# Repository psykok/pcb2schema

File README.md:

# pcb2schema

A KiCad addon that runs the design flow backwards: draw a PCB, get a schematic.

Drop footprints in the PCB editor, draw tracks between their pads, then run the
plugin. It works out which library symbol each footprint represents, recovers the
netlist from the copper you drew, places the symbols and routes the connections as
orthogonal wires. References are annotated back into the board and linked to the
generated symbols, so KiCad's normal schematic↔PCB sync keeps working afterwards.

Built and tested against **KiCad 10.0.6**.

## Why this is not straightforward

KiCad has no schematic API. `kicad-cli sch` only exports, and the IPC API covers the
board. So the `.kicad_sch` is generated directly as S-expressions, which means the
writer has to be exactly faithful to KiCad's own format — verified by round-tripping
every KiCad file on the system byte-for-byte.

The other half is that a freshly drawn board usually has **no nets at all**: every pad
and track sits on netcode 0. KiCad's ratsnest is useless in that state, but its
geometric hit-testing is not, and a union-find over pads, tracks, vias and zones
rebuilds the netlist from what is physically touching what.

## Installing

```sh
python3 tools/build_pcm.py            # -> dist/pcb2schema-<version>.zip
```

Then **Plugin and Content Manager → Install from File…** and pick the zip. Restart
pcbnew, or use *Tools → External Plugins → Refresh Plugins*.

This is the route to use. PCM reads `metadata.json` out of the archive as it installs
and records the result in `installed_packages.json`; it never reads it back from the
installed directory. So a package only has an author, description and version if PCM
put it there.

For development there is also

```sh
python3 tools/build_pcm.py --install  # copy straight into the plugin folder
```

which gets the code under the toolbar button without going through PCM. The trade-off
is that PCM has no record of it, so it appears in the package list with a blank author
and version 0.0. That listing is cosmetic -- the plugin itself works either way.

The installed layout matters and is easy to get wrong: KiCad imports each directory
under `<KICAD_3RD_PARTY>/plugins/` *as a Python module*, and skips any that has no
`__init__.py` at its top level. So the files must land at

```
~/Documents/KiCad/<ver>/3rdparty/plugins/pcb2schema/__init__.py
```

not one level deeper. The directory name also becomes the module name, so it has to be
a legal Python identifier — the dotted reverse-DNS identifier cannot be used here.
`build_pcm.py --install` does this and fails loudly if the marker file is missing.

## Using it

1. Open your board in the PCB editor and save it.
2. Close the **schematic** editor. The PCB editor can stay open — that's where the
   plugin runs from. Only eeschema is a conflict, because the `.kicad_sch` is written
   directly and would be discarded the next time eeschema saves. The board is updated
   in memory and saved by you as usual.
3. Click the **PCB to Schematic** toolbar button, or *Tools → External Plugins → PCB
   to Schematic*.
4. If anything is untagged, decide whether to auto-tag it (see below).
5. Confirm any footprints the matcher could not identify on its own.
6. Open the schematic to review.

Both files are backed up with a timestamp before anything is written.

### Two-step: arrange, then wire

The automatic placement is a grid. It echoes the board so the sheet is navigable, but
on any real design you will want to lay it out yourself — and the router should work
with *your* arrangement, not one you are about to discard. So the run can be split:

1. **Symbols only** — places every part and stops. Any existing wiring is left alone.
2. *Arrange the sheet in the schematic editor.*
3. **Nets only** — wires it up, keeping every symbol exactly where you put it.

The plugin asks which to do on each run; **Symbols and nets** does both in one pass and
is the default. From the command line:

```sh
tools/run_headless.py board.kicad_pcb --stage symbols   # place, then go arrange
tools/run_headless.py board.kicad_pcb --stage nets      # wire up your arrangement
```

Splitting the run changes only where things sit — the resulting netlist is identical
either way, which is asserted by a test.

Between the two steps the board may have moved on, so the second step reports what
changed: parts added, parts deleted, and footprints swapped for a different one.
Wiring against a stale sheet would otherwise produce a schematic that quietly
disagrees with the PCB.

### Re-running keeps what you have arranged

Symbol positions survive a re-run, and so does wiring. A net is redrawn only when
something about it actually changed — its name, its set of pins, or where those pins
sit. Everything else is left exactly as you arranged it, including routes you dragged
into shape by hand.

Move one symbol and only the nets touching it are redrawn; the rest of the sheet is
untouched. The run reports which is which:

```
Updated board.kicad_sch | 12 symbols, 10 nets, 8 net(s) left untouched
```

If part of a net's wiring has been deleted, that net is redrawn rather than left half
wired.

### Everything must be tagged first

A conversion is only as good as the identifiers it starts from. If footprints are
still `REF**` and nets are unnamed, the plugin would have to invent both — and then
write its inventions back onto your board. That is a naming decision, and it belongs
to you, so it is an explicit gate rather than a silent default.

Before generating anything the plugin checks for footprints with no reference
designator, duplicated references, and unnamed nets. If it finds any it stops, having
written nothing, and reports exactly what is missing. You can then either tag them
yourself in the PCB editor, or let the plugin do it:

```sh
tools/run_headless.py board.kicad_pcb            # reports and stops (exit 2)
tools/run_headless.py board.kicad_pcb --auto-tag # fills the gaps
```

Auto-tagging **only fills gaps**. It assigns the next free number to each untagged
item and never renames anything that already has one, so hand-assigned identifiers
survive untouched. Net numbering follows whatever convention the board already uses:
if your nets are called `1`, `2`, `3`, the next one is `4`, not `N$1`.

Duplicated references are reported but not fixed — which of two `R1`s should be
renamed is not something to guess at.

### Net names are preserved

Every net gets a **global** label carrying its name. This is not decoration: a wire
carries no name, so without a label KiCad renames the net `Net-(D1-A)`, and the next
*Update PCB from Schematic* pushes that back over the name you chose. Global rather
than local labels because KiCad prefixes a root-sheet local label with the sheet path
— a net called `1` would come back as `/1`.

### What it decides on its own

Everyday parts — resistors, capacitors, LEDs, diodes, crystals, fuses, switches, pin
headers, terminal blocks — are matched without asking, using the symbol's declared
footprint filters, its default footprint, and a curated hint table. Pin/pad
compatibility is a hard gate rather than a hint: a symbol whose pins cannot be
reconciled with the footprint's pads is never offered, however well it scores
otherwise.

Anything ambiguous goes to a picker showing the ranked candidates, why each was
suggested, and the pad-versus-pin comparison. A match that would need pads mapped to
pins positionally (`A`/`K` against `1`/`2`) is never auto-accepted — that is a guess
about polarity, and you should see it.

## Limitations

- **Placement is a grid, not a schematic layout.** Symbols keep their rough relative
  positions from the board, which makes the sheet navigable, but no attempt is made to
  produce a conventionally-drawn schematic (power at top, signal flow left to right).
- **Nets that cannot be routed become labels.** The result stays electrically correct;
  it just looks worse for that net. The run report lists them.
- **Genuinely unconnected pads stay unconnected.** No no-connect flags are inserted,
  so ERC will report them — that is usually a real layout problem worth seeing.
- **Duplicated references are not auto-fixed** — only reported.
- Placement of *new* symbols on an existing sheet is a grid slot, not a considered
  position; existing symbols never move.

## Development

Everything under `plugins/core/` is headless and must never import `wx`; the GUI layer
is confined to `plugins/action.py` and `plugins/ui/`. That is what lets the whole
pipeline be driven and tested without clicking through KiCad.

Tests run under KiCad's bundled interpreter, since `pcbnew` imports nowhere else, and
use a small built-in runner because that interpreter has no pytest:

```sh
/Applications/KiCad/KiCad.app/Contents/Frameworks/Python.framework/Versions/3.9/bin/python3 \
    tools/run_tests.py            # everything
    tools/run_tests.py netlist    # or filter by name
```

The load-bearing test is the **netlist round-trip** in `tests/test_convert.py`: a
generated schematic is fed back through KiCad's own netlist exporter and compared net
by net against the netlist recovered from the board. Wrong symbol, wrong pin mapping,
a pin snapped off-grid, a wire that doesn't quite touch, a missing junction — they all
surface there and essentially nowhere else.

`tests/fixtures.py` builds synthetic boards with known netlists. They exist because
the KiCad template projects, the obvious corpus, turn out to contain **zero tracks** —
they are unrouted shield outlines, so they exercise only the declared-net path and
cannot validate geometric recovery at all.

### Layout

| Path | |
|---|---|
| `plugins/core/sexpr.py` | lossless S-expression parse/serialise |
| `plugins/core/netlist.py` | netlist recovery from copper geometry |
| `plugins/core/symlib.py` | cached index of ~23k library symbols |
| `plugins/core/matcher.py` | footprint → symbol ranking |
| `plugins/core/symbody.py` | full symbol definitions, pin geometry |
| `plugins/core/place.py` | sheet placement |
| `plugins/core/route.py` | orthogonal wire router |
| `plugins/core/schematic.py` | `.kicad_sch` construction |
| `plugins/core/preflight.py` | the tagging gate and auto-increment |
| `plugins/core/annotate.py` | references, symbol links and nets into the PCB |
| `plugins/core/sync.py` | incremental update against a project on disk |
| `plugins/core/state.py` | ownership sidecar, so user edits survive re-runs |
| `plugins/core/convert.py` | the pipeline |

## Licence

MIT.

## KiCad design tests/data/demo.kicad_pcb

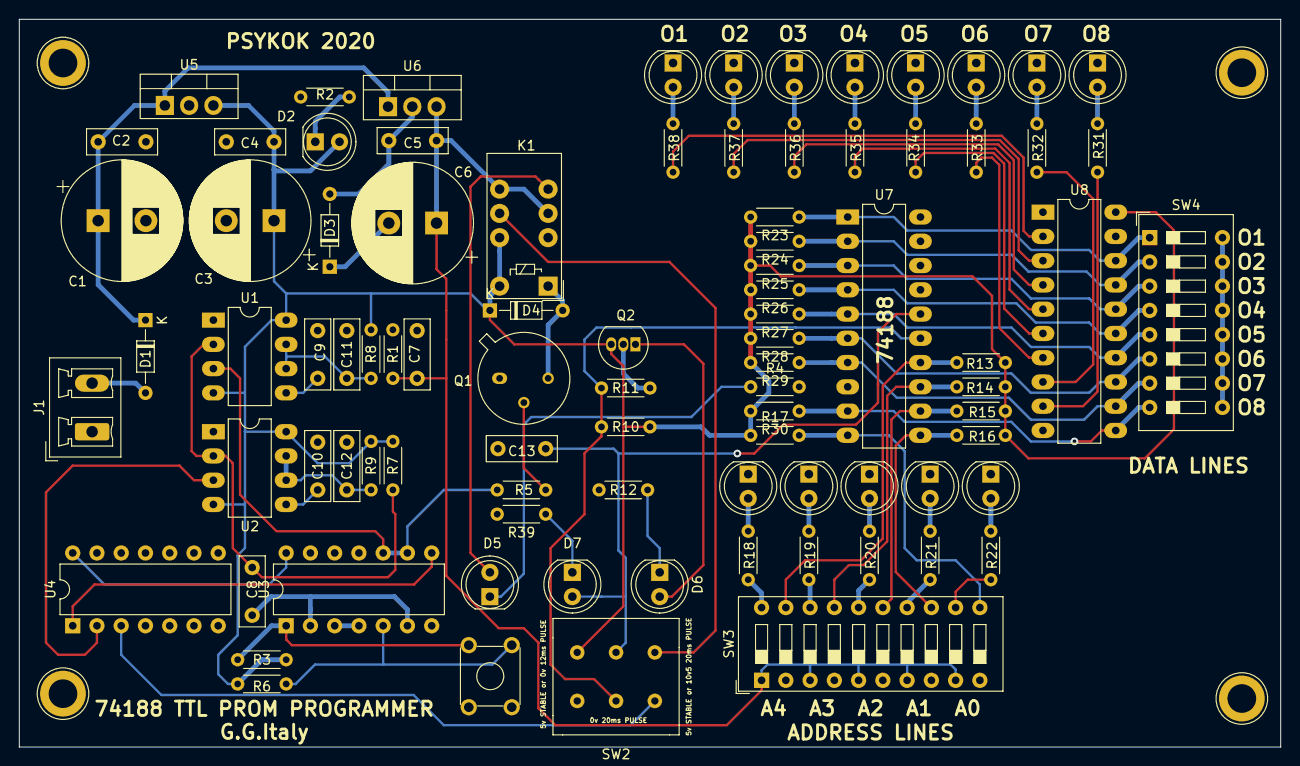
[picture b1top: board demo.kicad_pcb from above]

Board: 2 copper layers, 132.1 x 76.2 mm, 92 parts (0 on the bottom side), 70 nets.

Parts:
C1, C3: 470u 35v; CP_Radial_D12.5mm_P5.00mm
C2, C4, C5, C7, C11, C12, C13: 100n; C_Rect_L7.2mm_W2.5mm_P5.00mm_FKS2_FKP2_MKS2_MKP2
C6: 1000u 25v; CP_Radial_D12.5mm_P5.00mm
C8: 10n; C_Rect_L7.2mm_W2.5mm_P5.00mm_FKS2_FKP2_MKS2_MKP2
C9, C10: 33n; C_Rect_L7.2mm_W2.5mm_P5.00mm_FKS2_FKP2_MKS2_MKP2
D1: BYT12-1000; D_DO-34_SOD68_P7.62mm_Horizontal
D2, D8, D9, D10, D11, D12, D13, D14, D15, D16, D17, D18, D19, D20: LED; LED_D5.0mm
D3: BYT08-1000; D_DO-34_SOD68_P7.62mm_Horizontal
D4: SF4004; D_DO-34_SOD68_P7.62mm_Horizontal
D5: LED_RED; LED_D5.0mm
D6: LED_GREEN; LED_D5.0mm
D7: LED_BLUE; LED_D5.0mm
H1, H2, H3, H4: MountingHole; TestPoint_Loop_D3.80mm_Drill2.8mm
J1: Conn_01x02; PhoenixContact_MCV_1,5_2-G-5.08_1x02_P5.08mm_Vertical
K1: G6S-2; Relay_DPDT_Omron_G6S-2
Q1: BC140; TO-39-3
Q2: BC516; TO-92_Inline
R1: 150; R_Axial_DIN0204_L3.6mm_D1.6mm_P5.08mm_Horizontal
R2, R18, R19, R20, R21, R22, R39: 10k; R_Axial_DIN0204_L3.6mm_D1.6mm_P5.08mm_Horizontal
R3, R4, R6, R12: 2.2k; R_Axial_DIN0204_L3.6mm_D1.6mm_P5.08mm_Horizontal
R5, R31, R32, R33, R34, R35, R36, R37, R38: 1k; R_Axial_DIN0204_L3.6mm_D1.6mm_P5.08mm_Horizontal
R7, R10, R11: 47k; R_Axial_DIN0204_L3.6mm_D1.6mm_P5.08mm_Horizontal
R8: 180k; R_Axial_DIN0204_L3.6mm_D1.6mm_P5.08mm_Horizontal
R9: 68k; R_Axial_DIN0204_L3.6mm_D1.6mm_P5.08mm_Horizontal
R13, R14, R15, R16, R17: 1.5k; R_Axial_DIN0204_L3.6mm_D1.6mm_P5.08mm_Horizontal
R23, R24, R25, R26, R27, R28, R29, R30: 3.9k; R_Axial_DIN0204_L3.6mm_D1.6mm_P5.08mm_Horizontal
SW1: SW_Push_SPDT; SW_TH_Tactile_Omron_B3F-10xx
SW2: SW_Push_DPDT; SW_3POS
SW3: SW_DIP_x10; SW_DIP_SPSTx10_Slide_9.78x27.58mm_W7.62mm_P2.54mm
SW4: SW_DIP_x08; SW_DIP_SPSTx08_Slide_9.78x22.5mm_W7.62mm_P2.54mm
U1, U2: NE555; DIP-8_W7.62mm_LongPads
U3: 74LS00; DIP-14_W7.62mm
U4: 74LS32; DIP-14_W7.62mm
U5: L7805; TO-220-3_Vertical
U6: uA7810; TO-220-3_Vertical
U7: 74188; DIP-20_W7.62mm_LongPads
U8: 74LS245; DIP-20_W7.62mm_LongPads

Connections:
+5v: C3.1, C4.1, D2.2, D4.1, K1.10, K1.12, Q2.3, R3.2, R6.2, R7.2, R8.2, R9.2, R10.1, R13.1, R14.1, R15.1, R16.1, R17.1, R23.2, R24.2, R25.2, R26.2, R27.2, R28.2, R29.2, R30.2, SW2.1, U1.4, U1.8, U2.4, U2.8, U3.14, U4.14, U5.3, U8.20
+10v5: C5.1, C6.1, C7.1, K1.4, K1.8, R1.1, SW3.1, SW3.3, SW3.5, SW3.7, SW3.9, U6.3
GND: C1.2, C2.2, C3.2, C4.2, C6.2, C7.2, C9.2, C10.2, C11.2, C12.2, C13.2, D3.1, D8.1, D9.1, D10.1, D11.1, D12.1, D13.1, D14.1, D15.1, D16.1, D17.1, D18.1, D19.1, D20.1, J1.1, Q1.1, R1.2, R2.2, R4.2, R12.1, R39.2, SW1.2, SW2.4, SW3.2, SW3.4, SW3.6, SW3.8, SW3.10, SW4.9, SW4.10, SW4.11, SW4.12, SW4.13, SW4.14, SW4.15, SW4.16, U1.1, U2.1, U3.7, U4.7, U5.2, U7.8, U8.1, U8.10, U8.19
unnamed: C1.1, C2.1, D1.1, U5.1, U6.1
unnamed: C5.2, D3.2, U6.2
unnamed: C8.1, R7.1, U1.2, U2.2
unnamed: C8.2, U3.2, U3.6
unnamed: C9.1, U1.5
unnamed: C10.1, U2.5
unnamed: C11.1, R8.1, U1.6, U1.7
unnamed: C12.1, R9.1, U2.6, U2.7
unnamed: C13.1, D7.2, SW2.2, U7.16
unnamed: D1.2, J1.2
unnamed: D2.1, R2.1
unnamed: D4.2, K1.1, Q1.3
unnamed: D5.1, R4.1
unnamed: D5.2, K1.5
unnamed: D6.1, R12.2
unnamed: D6.2, Q2.1
unnamed: D7.1, R39.1
unnamed: D8.2, R18.1
unnamed: D9.2, R19.1
unnamed: D10.2, R20.1
unnamed: D11.2, R21.1
unnamed: D12.2, R22.1
unnamed: D13.2, R31.1
unnamed: D14.2, R32.1
unnamed: D15.2, R33.1
unnamed: D16.2, R34.1
unnamed: D17.2, R35.1
unnamed: D18.2, R36.1
unnamed: D19.2, R37.1
unnamed: D20.2, R38.1
unnamed: K1.9, SW2.3
unnamed: Q1.2, R5.1
unnamed: Q2.2, R11.2
unnamed: R3.1, SW1.3, U3.1
unnamed: R5.2, U1.3, U3.9, U3.10
unnamed: R6.1, SW1.1, U3.5
unnamed: R10.2, R11.1, SW2.5, U7.15
unnamed: R13.2, SW3.19, U7.14
unnamed: R14.2, SW3.17, U7.13
unnamed: R15.2, SW3.15, U7.12
unnamed: R16.2, SW3.13, U7.11
unnamed: R17.2, SW3.11, U7.10
unnamed: R18.2, SW3.20
unnamed: R19.2, SW3.18
unnamed: R20.2, SW3.16
unnamed: R21.2, SW3.14
unnamed: R22.2, SW3.12
unnamed: R23.1, SW4.1, U7.1, U8.18
unnamed: R24.1, SW4.2, U7.2, U8.17
unnamed: R25.1, SW4.3, U7.3, U8.16
unnamed: R26.1, SW4.4, U7.4, U8.15
unnamed: R27.1, SW4.5, U7.5, U8.14
unnamed: R28.1, SW4.6, U7.6, U8.13
unnamed: R29.1, SW4.7, U7.7, U8.12
unnamed: R30.1, SW4.8, U7.9, U8.11
unnamed: R31.2, U8.9
unnamed: R32.2, U8.8
unnamed: R33.2, U8.7
unnamed: R34.2, U8.6
unnamed: R35.2, U8.5
unnamed: R36.2, U8.4
unnamed: R37.2, U8.3
unnamed: R38.2, U8.2
unnamed: SW2.6, U4.3
unnamed: U2.3, U4.2
unnamed: U3.3, U3.4
unnamed: U3.8, U4.1

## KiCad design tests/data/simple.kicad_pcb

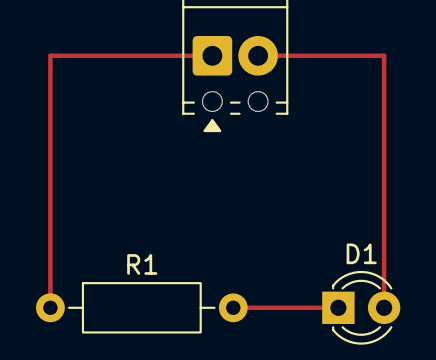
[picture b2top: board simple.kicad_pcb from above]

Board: 2 copper layers, 3 parts (0 on the bottom side), 3 nets.

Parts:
D1: LED_D3.0mm
J1: TerminalBlock_Phoenix_MPT-0,5-2-2.54_1x02_P2.54mm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; TerminalBlock_Phoenix_MPT-0,5-2-2.54_1x02_P2.54mm_Horizontal
R1: R_Axial_DIN0207_L6.3mm_D2.5mm_P10.16mm_Horizontal

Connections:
1: J1.1, R1.1
2: D1.2, J1.2
3: D1.1, R1.2
